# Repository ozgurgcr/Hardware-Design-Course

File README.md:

This repo is created for learning hardware design rules by following ESTEEM PCB course.
The PCB that contained here not tested or produced.

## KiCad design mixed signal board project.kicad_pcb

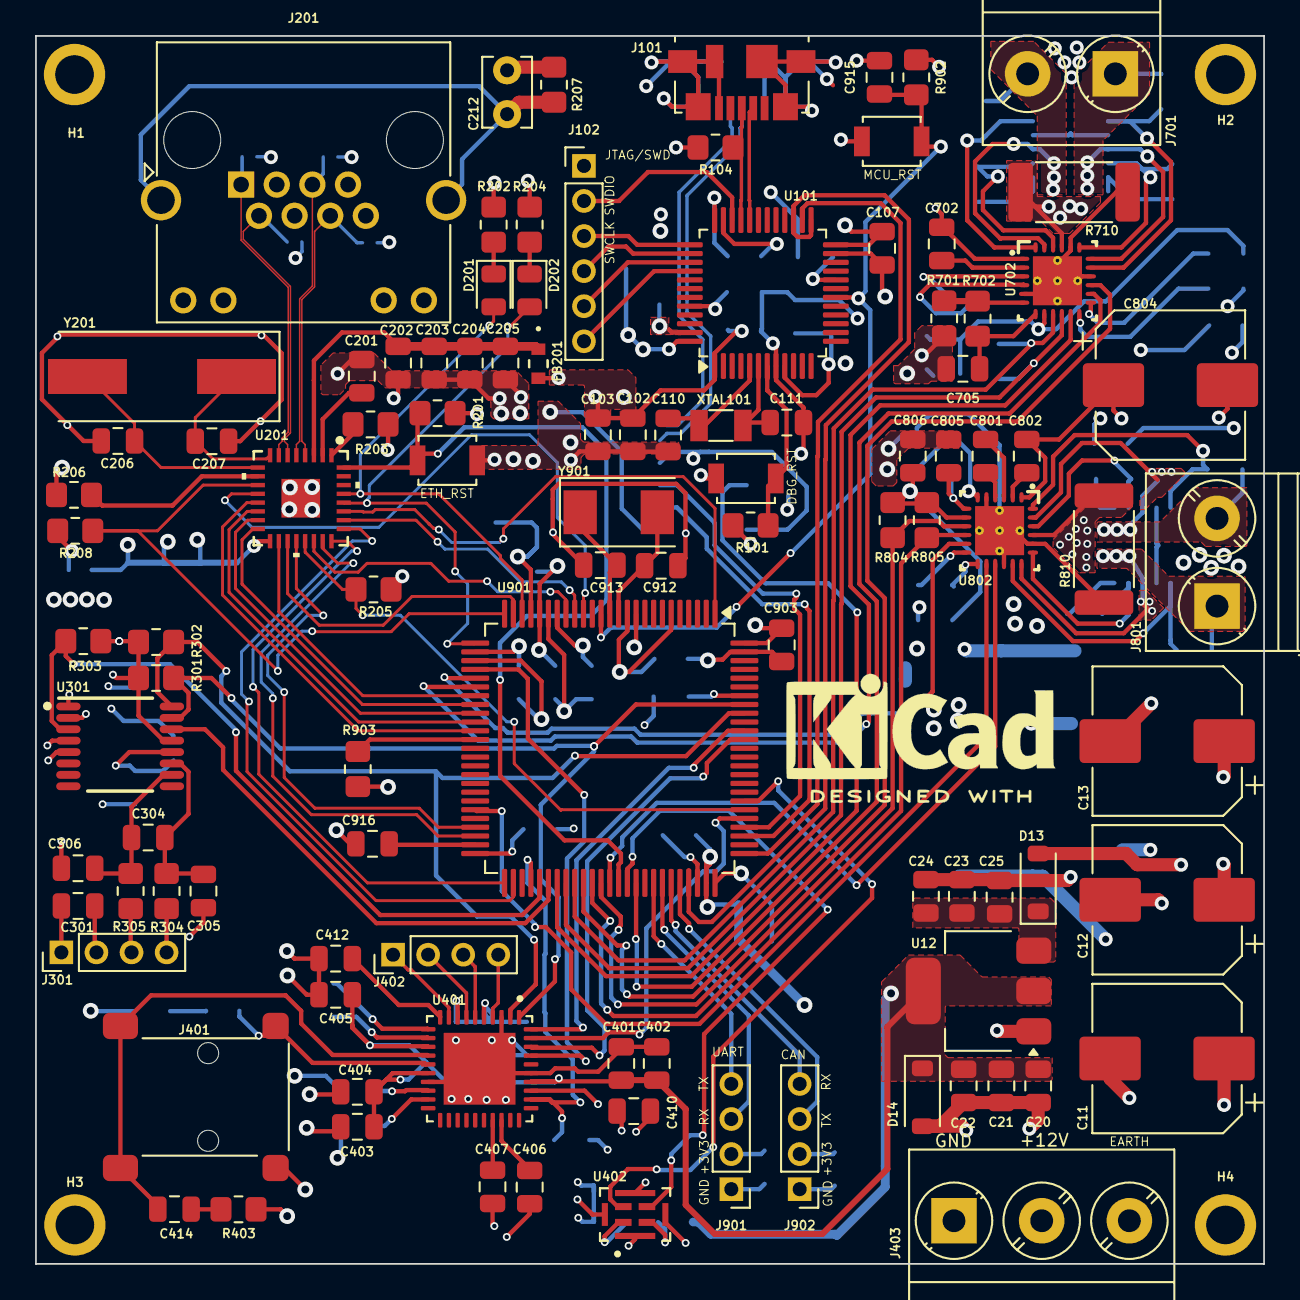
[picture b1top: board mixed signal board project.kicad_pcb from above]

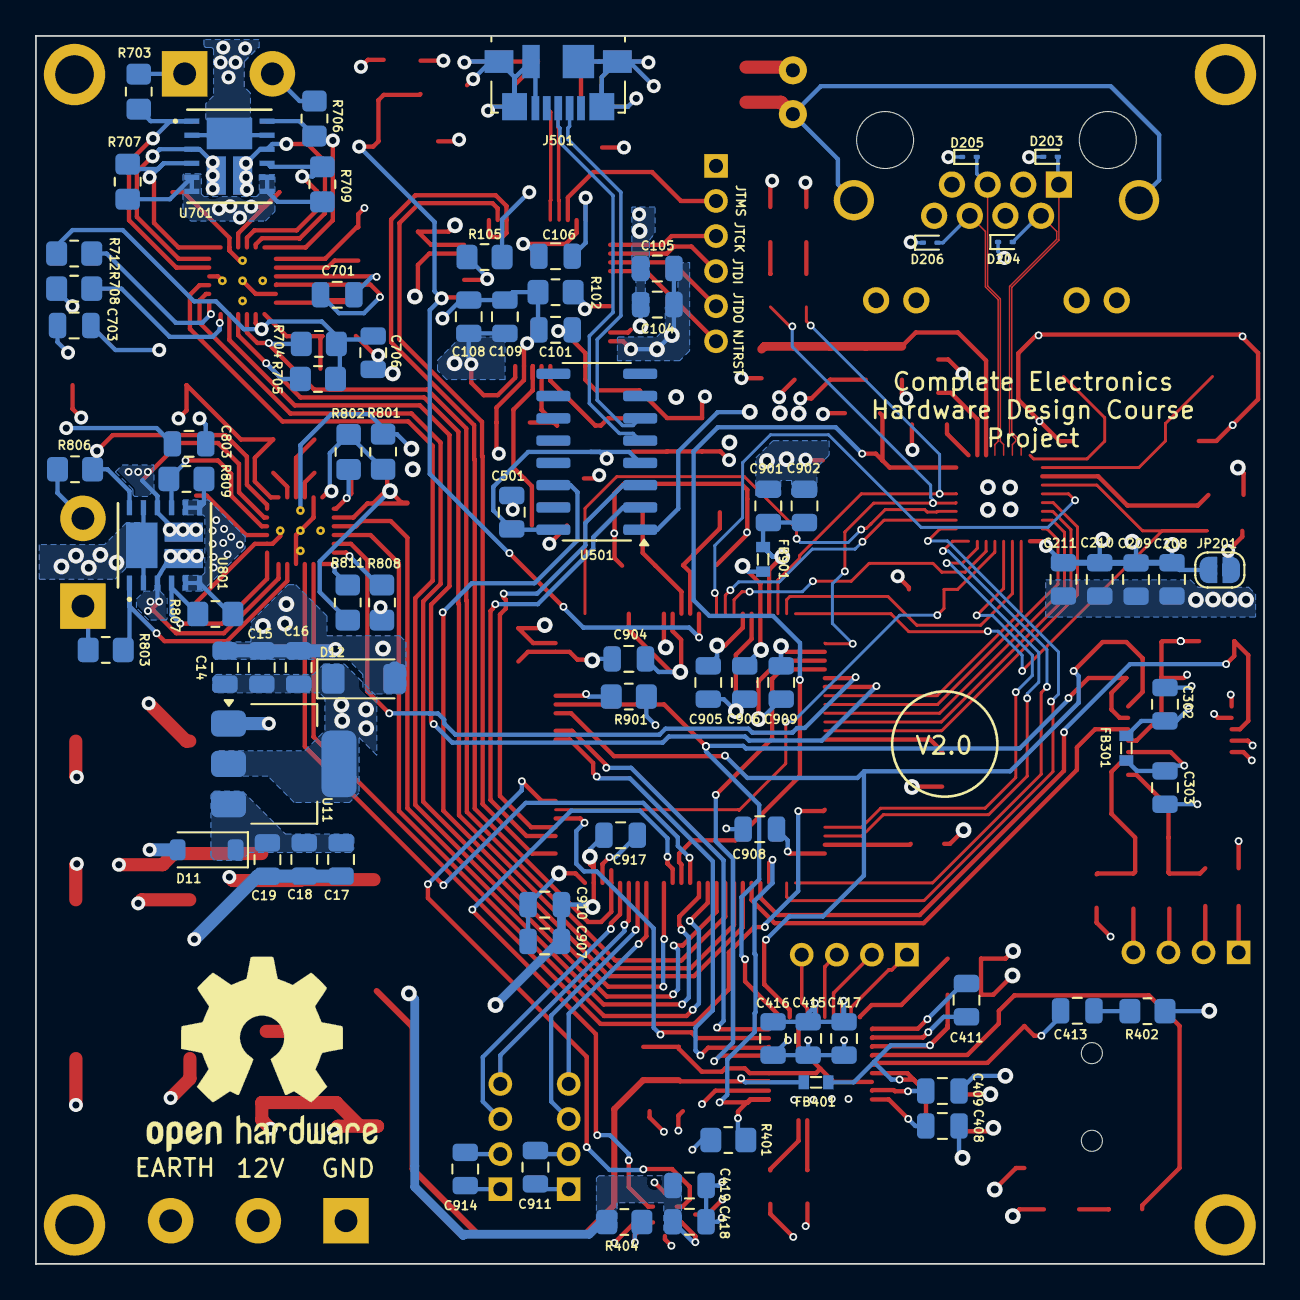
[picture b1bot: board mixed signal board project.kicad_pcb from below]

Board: 4 copper layers, 70.0 x 70.0 mm, 188 parts (81 on the bottom side), 145 nets.

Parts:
C11, C12, C13, C804: 100u; CP_Elec_8x10
C14, C17, C20, C23, C102, C301, C302, C303, C304, C402, C404, C405, C410, C415, C417, C419, C501, C701, C703, C801, C803, C902, C903, C904, C905, C906, C908, C909, C910, C911, C914, C915: 0.1u; C_0805_2012Metric
C15, C18, C21, C24, C109, C203, C210, C401, C403, C408, C411, C412, C418, C702, C705, C706, C802, C805, C806, C901: 1u; C_0805_2012Metric
C16, C19, C22, C25, C202, C211, C409, C416: 10u; C_0805_2012Metric
C101, C907: 4.7u; C_0805_2012Metric
C103, C104, C105, C106, C107, C204, C209: 100n; C_0805_2012Metric
C108, C205, C208, C305, C306: 10n; C_0805_2012Metric
C110, C111, C912, C913: 30p; C_0805_2012Metric
C201: 2n; C_0805_2012Metric
C206, C207: 20p; C_0805_2012Metric
C212: 10n; C_Disc_D3.8mm_W2.6mm_P2.50mm
C406, C407: 150p; C_0805_2012Metric
C413, C414: 22n; C_0805_2012Metric
C916, C917: 2.2u; C_0805_2012Metric
D11, D13: MBR0530; D_SOD-123
D12: BZV55B3V3; D_MiniMELF
D14: D_Zener; D_SOD-123
D201, D202: LED; LED_0805_2012Metric
D203, D204, D205, D206: ESD9B3.3ST5G; D_SOD-923
FB201: 1k_100MHz; IND_1608_TDK
FB301, FB401: 1k; 0603
FB901: FerriteBead_Small; 0603
H1, H2, H3, H4: MountingHole; MountingHole_2.2mm_M2_ISO7380_Pad
J101, J501: USB_B_Mini; USB_Micro-B_Molex_47346-0001
J102: Conn_01x06_Pin; PinHeader_1x06_P2.00mm_Vertical
J201: 8P8C_Shielded; RJ45_Amphenol_RJHSE538X
J301, J402: Conn_01x04_Pin; PinHeader_1x04_P2.00mm_Vertical
J401: AudioJack3; Jack_3.5mm_Lumberg_1503_02_Horizontal
J403: Screw_Terminal_01x03; TerminalBlock_Phoenix_PT-1,5-3-5.0-H_1x03_P5.00mm_Horizontal
J701, J801: Conn_01x02_Socket; TerminalBlock_Phoenix_PT-1,5-2-5.0-H_1x02_P5.00mm_Horizontal
J901: UART_CONN; PinHeader_1x04_P2.00mm_Vertical
J902: CAN_CONN; PinHeader_1x04_P2.00mm_Vertical
JP201: SolderJumper_2_Open; SolderJumper-2_P1.3mm_Open_RoundedPad1.0x1.5mm
R101, R201, R203, R205, R208, R301, R302, R404, R703, R704, R705, R706, R707, R709, R803, R804, R805, R806, R807, R809: 10k; R_0805_2012Metric_Pad1.20x1.40mm_HandSolder
R102, R105, R303, R712, R811, R901, R902, R903: 100k; R_0805_2012Metric_Pad1.20x1.40mm_HandSolder
R104: 1.5k; R_0805_2012Metric_Pad1.20x1.40mm_HandSolder
R202, R204, R701, R801: 3k3; R_0805_2012Metric_Pad1.20x1.40mm_HandSolder
R206: 6k49; R_0805_2012Metric_Pad1.20x1.40mm_HandSolder
R207: 1M; R_0805_2012Metric_Pad1.20x1.40mm_HandSolder
R304, R305: 1k; R_0805_2012Metric_Pad1.20x1.40mm_HandSolder
R401: 10K; R_0805_2012Metric_Pad1.20x1.40mm_HandSolder
R402, R403: 51.1; R_0805_2012Metric_Pad1.20x1.40mm_HandSolder
R702, R802: 2k; R_0805_2012Metric_Pad1.20x1.40mm_HandSolder
R708, R808: 33k; R_0805_2012Metric_Pad1.20x1.40mm_HandSolder
R710, R810: 50M; R_2512_6332Metric_Pad1.40x3.35mm_HandSolder
SW101, SW201, SW901: SW_SPDT; SW_SPST_B3U-1000P
U11: LD1117S33TR_SOT223; SOT-223-3_TabPin2
U12: LD1117S18TR_SOT223; SOT-223-3_TabPin2
U101: STM32F103C8Tx; LQFP-48_7x7mm_P0.5mm
U201: DP83826ERHBR; QFN_ERHBR_TEX
U301: ADS122C04IPW; PW0016A_N
U401: CS43L22-CNZ; QFN50P600X600X100-41N
U402: IMP34DT05TR; MIC_MP34DT06JTR
U501: CH340C; SOIC-16_3.9x9.9mm_P1.27mm
U701, U801: DMHT6016LFJ-13; V-DFN5045-12_DIO
U702, U802: DRV8701; RGE0024F
U901: STM32F407VGTx; LQFP-100_14x14mm_P0.5mm
XTAL101: NX3225GD-8MHZ-STD-CRA-3; Crystal_SMD_3215-2Pin_3.2x1.5mm
Y201: 25Mhz; Crystal_SMD_HC49-SD
Y901: 8MHz; Crystal_SMD_0603-2Pin_6.0x3.5mm

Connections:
+1V8: C20.1, C21.1, C22.1, C401.1, C402.1, C418.1, C419.1, D14.1 (K), FB401.2, R404.2, U12.2 (VO), U401.34 (VD), U402.1 (VDD)
+3.3VA: C202.2, C203.2, C204.2, C205.2, FB201.1, U201.3 (VDDA3V3)
+3V3: C14.1, C15.1, C16.1, C101.1, C102.1, C103.1, C104.1, C105.1, C106.1, C107.1, C108.1, C109.1, C208.1, C209.1, C210.1, C211.1, C301.1, C302.1, C410.1, C415.1, C416.1, C417.1, C501.1, C903.1, C904.1, C905.1, C906.1, C907.1, C908.1, C909.1, C910.1, C911.1, C914.1, D12.1 (K), FB201.2, FB301.1, FB901.2, J301.2, J901.2, J902.2, JP201.2 (B), R101.2, R104.1, R201.1, R203.1, R205.1, R301.1, R302.1, R303.1, R401.1, R902.1, U11.2 (VO), U101.1 (VBAT), U101.9 (VDDA), U101.24 (VDD), U101.36 (VDD), U101.48 (VDD), U201.17 (VDDIO), U301.13 (DVDD), U401.5 (VP), U401.8 (VP), U401.33 (VL), U501.4 (V3), U501.16 (VCC), U901.6 (VBAT), U901.11 (VDD), U901.19 (VDD), U901.21 (VREF+), U901.28 (VDD), U901.50 (VDD), U901.75 (VDD), U901.100 (VDD)
+12V: C11.1, C12.1, C13.1, C702.1, C703.1, C802.1, C803.1, C804.1, D11.2 (A), D13.2 (A), J403.2, U701.2 (D1/D4), U701.11 (D1/D4), U701.13 (D1/D4), U702.1 (VM), U801.2 (D1/D4), U801.11 (D1/D4), U801.13 (D1/D4), U802.1 (VM)
/ADC/AIN0_ADC: J301.4, R304.1
/ADC/AIN1_ADC: J301.3, R305.1
/ADC/RESET_ADC: R303.2, U301.3 (RESET_N), U901.55 (PD8)
/ADC/SCL: R302.2, U301.16 (SCL), U401.2 (SCL), U901.92 (PB6)
/ADC/SDA: R301.2, U301.15 (SDA), U401.1 (SDA), U901.93 (PB7)
/ADC/~DRDY_ADC: U301.14 (DRDY_N), U901.56 (PD9)
/DAC adn MIC/CLK_MIC: U402.3 (CLK), U901.65 (PC8)
/DAC adn MIC/DOUT_MIC: U402.4 (DOUT), U901.82 (PD1)
/DAC adn MIC/LRCK_DAC: U401.40 (LRCK), U901.90 (PB4)
/DAC adn MIC/MCLK_DAC: U401.37 (MCLK), U901.29 (PA4)
/DAC adn MIC/SCLK_DAC: U401.38 (SCLK), U901.89 (PB3)
/DAC adn MIC/SDIN_DAC: U401.39 (SDIN), U901.80 (PC12)
/DAC adn MIC/SPKR_OUTA_N: J402.3, U401.6 (SPKR_OUTA_M)
/DAC adn MIC/SPKR_OUTA_P: J402.4, U401.4 (SPKR_OUTA_P)
/DAC adn MIC/SPKR_OUTB_N: J402.1, U401.9 (SPKR_OUTB_M)
/DAC adn MIC/SPKR_OUTB_P: J402.2, U401.7 (SPKR_OUTB_P)
/DAC adn MIC/VA: C403.1, C404.1, C405.1, FB401.1, U401.13 (VHP_P), U401.16 (VA)
/DAC adn MIC/~RESET_DAC: R401.2, U401.32 (~RESET), U901.54 (PB15)
/Debugger/BOOT0: R102.2, U101.44 (BOOT0)
/Debugger/BOOT1: R105.2, U101.20 (PB2)
/Debugger/JTCK/SWCLK: J102.3, U101.37 (PA14)
/Debugger/JTCLK_F407: U101.26 (PB13), U901.76 (PA14)
/Debugger/JTDI: J102.4, U101.38 (PA15)
/Debugger/JTDO: J102.5, U101.39 (PB3)
/Debugger/JTMS_F407: U101.25 (PB12), U101.27 (PB14), U901.72 (PA13)
/Debugger/JTMS/SWDIO: J102.2, U101.34 (PA13)
/Debugger/NJTRST: J102.6, U101.40 (PB4)
/Debugger/NRST: R101.1, SW101.2, U101.7 (NRST)
/Debugger/USBD_N: J101.2 (D-), U101.32 (PA11)
/Debugger/USBD_P: J101.3 (D+), R104.2, U101.33 (PA12)
/Ethernet/CEXT: C201.2, U201.2 (CEXT)
/Ethernet/ETH_COL: D202.2 (A), U201.28 (COL/LED2/GPIO/Strap4), U901.26 (PA3)
/Ethernet/ETH_CRS: D201.2 (A), U201.29 (CRS/LED3/Strap3), U901.23 (PA0)
/Ethernet/ETH_INT: R205.2, U201.21 (PWRDN/INT), U901.81 (PD0)
/Ethernet/ETH_MDC: U201.12 (MDC), U901.16 (PC1)
/Ethernet/ETH_MDIO: R208.2, U201.11 (MDIO), U901.25 (PA2)
/Ethernet/ETH_RX_CLK: U201.19 (RX_CLK/50MHz_RMII), U901.24 (PA1)
/Ethernet/ETH_RX_D0: U201.16 (Strap0/RX_D0), U901.33 (PC4)
/Ethernet/ETH_RX_D1: U201.15 (Strap9/RX_D1), U901.34 (PC5)
/Ethernet/ETH_RX_D2: U201.14 (Strap8/RX_D2), U901.35 (PB0)
/Ethernet/ETH_RX_D3: U201.13 (Strap7/RX_D3), U901.36 (PB1)
/Ethernet/ETH_RX_DV: U201.18 (RX_DV/CRS_DV/Strap10), U901.32 (PA7)
/Ethernet/ETH_RX_ER: U201.20 (RX_ER/Strap6), U901.47 (PB10)
/Ethernet/ETH_TX_CLK: U201.22 (TX_CLK/Strap5), U901.18 (PC3)
/Ethernet/ETH_TX_D0: U201.24 (TX_D0), U901.51 (PB12)
/Ethernet/ETH_TX_D1: U201.25 (TX_D1), U901.52 (PB13)
/Ethernet/ETH_TX_D2: U201.26 (TX_D2), U901.17 (PC2)
/Ethernet/ETH_TX_D3: U201.27 (TX_D3), U901.1 (PE2)
/Ethernet/ETH_TX_EN: U201.23 (TX_EN), U901.48 (PB11)
/Ethernet/ETH_XI: C206.2, U201.9 (XI/50MHzIn), Y201.2
/Ethernet/ETH_XO: C207.2, U201.8 (XO), Y201.1
/Ethernet/MODE_SEL: R203.2, U201.1 (ModeSelect)
/Ethernet/RD_N: D206.2 (A2), J201.6, U201.4 (RD_M)
/Ethernet/RD_P: D205.2 (A2), J201.5, U201.5 (RD_P)
/Ethernet/RESET_PHY: R201.2, SW201.2, U201.32 (RST_N), U901.64 (PC7)
/Ethernet/RJ_45_SH: C212.1, J201.SH, R207.1
/Ethernet/R_BIAS: R206.1, U201.10 (RBIAS)
/Ethernet/TD_N: D204.2 (A2), J201.2, U201.6 (TD_M)
/Ethernet/TD_P: D203.2 (A2), J201.1, U201.7 (TD_P)
/Motor_Driver1/EN: U802.14 (EN), U901.45 (PE14)
/Motor_Driver1/GH1: R803.2, U801.1 (G1), U802.17 (GH1)
/Motor_Driver1/GH2: R806.2, U801.12 (G4), U802.24 (GH2)
/Motor_Driver1/GL1: R807.2, U801.4 (G2), U802.19 (GL1)
/Motor_Driver1/GL2: R809.2, U801.9 (G3), U802.22 (GL2)
/Motor_Driver1/PH: U802.15 (PH), U901.63 (PC6)
/Motor_Driver1/SH1: J801.1, R803.1, U801.3 (S1/D2), U801.14 (S1/D2), U802.18 (SH1)
/Motor_Driver1/SH2: J801.2, R806.1, U801.10 (S4/D3), U801.15 (S4/D3), U802.23 (SH2)
/Motor_Driver1/SNSOUT: R805.1, U802.10 (SNSOUT), U901.61 (PD14)
/Motor_Driver1/SO: U802.11 (SO), U901.30 (PA5)
/Motor_Driver1/SP: R807.1, R809.1, R810.2, U801.5 (S2), U801.6 (S2), U801.7 (S3), U801.8 (S3), U802.21 (SP)
/Motor_Driver1/nFAULT: R804.2, U802.9 (nFAULT), U901.62 (PD15)
/Motor_Driver2/EN_2: U702.14 (EN), U901.66 (PC9)
/Motor_Driver2/GH1_2: R703.2, U701.1 (G1), U702.17 (GH1)
/Motor_Driver2/GH2_2: R706.2, U701.12 (G4), U702.24 (GH2)
/Motor_Driver2/GL1_2: R707.2, U701.4 (G2), U702.19 (GL1)
/Motor_Driver2/GL2_2: R709.2, U701.9 (G3), U702.22 (GL2)
/Motor_Driver2/PH_2: U702.15 (PH), U901.60 (PD13)
/Motor_Driver2/SH1_2: J701.1, R703.1, U701.3 (S1/D2), U701.14 (S1/D2), U702.18 (SH1)
/Motor_Driver2/SH2_2: J701.2, R706.1, U701.10 (S4/D3), U701.15 (S4/D3), U702.23 (SH2)
/Motor_Driver2/SNSOUT_2: R705.1, U702.10 (SNSOUT), U901.58 (PD11)
/Motor_Driver2/SO_2: U702.11 (SO), U901.31 (PA6)
/Motor_Driver2/SP_2: R707.1, R709.1, R710.2, U701.5 (S2), U701.6 (S2), U701.7 (S3), U701.8 (S3), U702.21 (SP)
/Motor_Driver2/nFAULT_2: R704.2, U702.9 (nFAULT), U901.59 (PD12)
/STM32F407/CAN_RX: J902.4, U901.70 (PA11)
/STM32F407/CAN_TX: J902.3, U901.71 (PA12)
/STM32F407/CH340_RXD: U501.3 (RXD), U901.79 (PC11)
/STM32F407/CH340_TXD: U501.2 (TXD), U901.78 (PC10)
/STM32F407/CH340_~RST: U501.14 (~RTS), U901.57 (PD10)
/STM32F407/EXT_UART_RX: J901.3, U901.69 (PA10)
/STM32F407/EXT_UART_TX: J901.4, U901.68 (PA9)
/STM32F407/NTRST_F407: C915.1, R902.2, SW901.2, U101.18 (PB0), U901.14 (NRST)
/USB_to_TTL/CH340_DN: J501.2 (D-), U501.6 (UD-)
/USB_to_TTL/CH340_DP: J501.3 (D+), U501.5 (UD+)
DVDD_1: C806.1, R804.1, R805.2, R811.2, U802.8 (DVDD)
DVDD_2: C706.1, R704.1, R705.2, R712.2, U702.8 (DVDD)
Earth: C212.2, H1.1, R207.2
Earth_2: H4.1, J403.3
GND: C11.2, C12.2, C13.2, C14.2, C15.2, C16.2, C17.2, C18.2, C19.2, C20.2, C21.2, C22.2, C23.2, C24.2, C25.2, C101.2, C102.2, C103.2, C104.2, C105.2, C106.2, C107.2, C108.2, C109.2, C110.1, C111.1, C201.1, C202.1, C203.1, C204.1, C205.1, C206.1, C207.1, C208.2, C209.2, C210.2, C211.2, C301.2, C302.2, C303.2, C305.2, C306.2, C401.2, C402.2, C403.2, C404.2, C405.2, C406.2, C407.2, C408.2, C409.2, C410.2, C412.2, C415.2, C416.2, C417.2, C418.2, C419.2, C501.2, C703.2, C705.2, C706.2, C803.2, C804.2, C805.2, C806.2, C901.2, C902.2, C903.2, C904.2, C905.2, C906.2, C907.2, C908.2, C909.2, C910.2, C911.2, C912.1, C913.1, C914.2, C915.2, C916.2, C917.2, D12.2 (A), D14.2 (A), D203.1 (A1), D204.1 (A1), D205.1 (A1), D206.1 (A1), J101.5 (GND), J101.6 (Shield), J102.1, J301.1, J401.S, J403.1, J501.5 (GND), J501.6 (Shield), J901.1, J902.1, R102.1, R105.1, R202.2, R204.2, R206.2, R402.2, R403.2, R701.2, R708.1, R710.1, R801.2, R808.1, R810.1, R901.2, R903.2, SW101.1, SW201.1, SW901.1, U11.1 (GND), U12.1 (GND), U101.8 (VSSA), U101.23 (VSS), U101.35 (VSS), U101.47 (VSS), U201.33 (GND), U301.1 (A0), U301.2 (A1), U301.4 (DGND), U301.5 (AVSS), U401.3 (AD0), U401.17 (AGND), U401.35 (DGND), U401.41 (GND), U402.5 (GND), U402.6 (GND), U402.7 (GND), U402.8 (GND), U501.1 (GND), U702.5 (GND), U702.16 (GND), U702.20 (SN), U702.25 (GND), U802.5 (GND), U802.16 (GND), U802.20 (SN), U802.25 (GND), U901.10 (VSS), U901.20 (VSSA), U901.27 (VSS), U901.74 (VSS), U901.99 (VSS)
unnamed: C413.2, R402.1
unnamed: C414.2, R403.1
unnamed: C17.1, C18.1, C19.1, D11.1 (K), U11.3 (VI)
unnamed: C23.1, C24.1, C25.1, D13.1 (K), U12.3 (VI)
unnamed: D201.1 (K), R202.1
unnamed: D202.1 (K), R204.1
unnamed: JP201.1 (A), R208.1
unnamed: C110.2, U101.5 (PD0), XTAL101.2
unnamed: C111.2, U101.6 (PD1), XTAL101.1
unnamed: C304.1, C305.1, R304.2, U301.11 (AIN0)
unnamed: C304.2, C306.1, R305.2, U301.10 (AIN1)
unnamed: C303.1, FB301.2, U301.12 (AVDD)
unnamed: C407.1, U401.27 (AFILTA)
unnamed: C406.1, U401.28 (AFILTB)
unnamed: C409.1, U401.18 (FILT_P)
unnamed: C411.2, U401.11 (FLYN)
unnamed: C411.1, U401.12 (FLYP)
unnamed: C413.1, J401.R, U401.15 (HP/LINE_OUTA)
unnamed: C414.1, J401.T, U401.14 (HP/LINE_OUTB)
unnamed: C412.1, U401.10 (VHPFILT_M)
unnamed: C408.1, U401.19 (VQ)
unnamed: R404.1, U402.2 (LR)
unnamed: C705.1, R702.1, U702.7 (AVDD)
unnamed: C701.2, U702.3 (CPH)
unnamed: C701.1, U702.4 (CPL)
unnamed: R708.2, U702.12 (IDRIVE)
unnamed: C702.2, U702.2 (VCP)
unnamed: R701.1, R702.2, U702.6 (VREF)
unnamed: R712.1, U702.13 (nSLEEP)
unnamed: C805.1, R802.1, U802.7 (AVDD)
unnamed: C801.2, U802.3 (CPH)
unnamed: C801.1, U802.4 (CPL)
unnamed: R808.2, U802.12 (IDRIVE)
unnamed: C802.2, U802.2 (VCP)
unnamed: R801.1, R802.2, U802.6 (VREF)
unnamed: R811.1, U802.13 (nSLEEP)
unnamed: R901.1, U901.94 (BOOT0)
unnamed: R903.1, U901.37 (PB2)
unnamed: C912.2, U901.12 (PH0), Y901.2
unnamed: C913.2, U901.13 (PH1), Y901.1
unnamed: C916.1, U901.49 (VCAP_1)
unnamed: C917.1, U901.73 (VCAP_2)
unnamed: C901.1, C902.1, FB901.1, U901.22 (VDDA)

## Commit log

2024-07-07 experimental branch created to do some changes in layout.
2024-07-07 some changes on experimente branch, layout, 12v and gnd tracks of power jack deleted.
2024-07-07 layout re-design start
2024-07-07 ethernet, debugger and usb layouts re-designed
2024-07-07 adc, dac and mi layouts re-designing...
2024-07-08 all layouts re-designed.Next step routing...
2024-07-08 ethernet, usb and motor driver-2 block routed, analog and digital planes seperated
2024-07-09 ADC layout reworked, analog and digital ground reworked, other blocks layout have to rework :( ...
2024-07-09 motor driver nsleep pin pull-up resistor connected 12V plane by 3.3V voltage divider.
2024-07-09 1.8V voltage regülator block placed in top side to provide a solid return path
2024-07-09 MIC footprint changed, all blocks routed internally, next step is route all to the MCU
2024-07-10 critical nets coloured,some tracks rerouted, section 9 completed.
2024-07-11 ethernet PHY tracks connected to MCU, reset pin left.
2024-07-11 I2C pins that is on ADC and DAC corrected
2024-07-11 All tracks routed, ERC done, waiting for PDN Analysis.
2024-07-12 schematic pages are reviewed
2024-07-12 PCB silk screen arranged
2024-07-12 Course Completed ! ! !
2024-07-12 some design failures reviewed(MIC VDD is 1V8, Motor Drivers' pull-up to DVDD pin, I2C net fixed). Routing mostly done.
2024-07-13 all tracks routed, ERC checked, silkscreens reviewed. Next step is PDN Analysis
2024-07-13 some additions
2024-07-17 Discard PDN file
